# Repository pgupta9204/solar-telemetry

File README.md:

# Solar Telemetry: Sub-8g Avian Wildlife Telemetry Node

An ultra-lightweight ($<8.0\text{g}$), perpetually energy-autonomous telemetry beacon engineered for avian wildlife conservation and asset tracking. Colloquially conceived as a "Solar AirTag", the system is architected from the ground up to replace heavy, battery-limited commercial tags with a sub-GHz RF beacon powered by solar energy harvesting.

---

## 1. Architectural Motivation

### 1.1 Avian Wildlife Conservation & The 5% Mass Rule
In wildlife telemetry and ornithological research, animal welfare dictates strict physical constraints:
* **The 5% Body-Mass Rule:** International ethical guidelines require that any tracking apparatus must not exceed **3-5%** of the bird's total body mass. Exceeding this limit impairs flight biomechanics, elevates metabolic expenditure, disrupts hunting, and skews behavioral data.
* **The Target Demographic:** Small-to-medium raptors—such as the American Kestrel (*Falco sparverius*, adult mass 100-140g), small falcons, and migratory shorebirds—have historically been excluded from continuous tracking due to the sheer bulk of existing hardware.
* **Limitations of Existing Commercial Tags:** Commercial avian trackers typically weigh >15-30g, cost upwards of \$1,500, and rely on non-rechargeable primary lithium cells that die within months, requiring recapture or terminating studies prematurely.

This project addresses this conservation bottleneck by engineering a complete telemetry solution under **8.0g total mass** (with a bare-board electronic budget of <3.0g capable of indefinite operation via ambient solar energy.

### 1.2 Electrical Engineering Scope & Design Objectives
This repository encapsulates a complete hardware development lifecycle:
* **KiCad EDA Workflow:** Schematic capture, hierarchical netlist design, custom symbol/footprint creation with 3D STEP modeling, and 4-layer PCB layout.
* **Controlled-Impedance RF Routing:** $50\Omega$ coplanar waveguide design and $\Pi$-matching network synthesis for Sub-GHz ISM frequencies (915 MHz / 868 MHz).
* **Ultra-Low-Power (ULP) Power Architecture:** Integration of maximum power point tracking (MPPT) solar harvesting with sub-microamp quiescent sleep states.
* **Event-Driven Firmware Architecture:** Hardware-level asynchronous interrupt handling to decouple sensing from compute and transmission.

---

## 2. Engineering Criteria & Constraints

| Parameter | Target Constraint | Design Implementation |
| :--- | :--- | :--- |
| **Total System Mass** | $m \le 8.0\text{g}$ (Target: $6.4\text{g}$) | Lightweight 4-layer $0.8\text{mm}$ PCB, miniature passives, SLA resin enclosure. |
| **Power Autonomy** | Net-Positive Diurnal Balance ($\Delta E_{\text{day}} > 0$) | e-peas AEM10941 PMIC + flexible solar cell + 35 mAh LiPo buffer. |
| **Deep-Sleep Current** | $I_{\text{sleep}} \le 2.5\,\mu\text{A}$ at $3.3\text{V}$ | STM32WL55 in Stop2 mode ($1.2\,\mu\text{A}$) + LIS2DW12 low-power sensing ($0.38\,\mu\text{A}$). |
| **RF Carrier Frequency** | $915\,\text{MHz}$ (US) / $868\,\text{MHz}$ (EU) | Sub-GHz ISM band for extended line-of-sight propagation ($>5\text{-}15\\text{km}$). |
| **RF Trace Impedance** | $Z_0 = 50.0\,\Omega \pm 5\%$ | JLC7628 stackup microstrip trace geometry with continuous L2 ground plane. |
| **Board Footprint** | $20.0 \text{mm} \times 25.0 \text{mm}$ | High-density component placement (0402 passives, UFQFPN-48, QFN-28). |

### Strict Mass Budget Breakdown ($6.4\text{g}$ Target)

| Subsystem | Component Details | Allocated Mass |
| :--- | :--- | :--- |
| **Bare PCB** | 4-Layer FR4 ($0.8\text{mm}$ core, $20\text{mm} \times 25\text{mm}$) | $0.8\text{g}$ |
| **Core Electronics** | STM32WL55 SoC, LIS2DW12 IMU, 0402/0603 passives | $0.6\text{g}$ |
| **Energy Harvester** | e-peas AEM10941 PMIC + 3V flexible solar cell | $0.7\text{g}$ |
| **Energy Buffer** | $3.7\text{V}$ 35 mAh ultra-light LiPo pouch cell | $1.8\text{g}$ |
| **RF Antenna System** | $50\Omega$ $\Pi$-network + $8.2\text{cm}$ micro-wire monopole | $0.3\text{g}$ |
| **Protective Housing** | SLA 3D-printed light-cured resin ($0.8\text{mm}$ wall) | $2.2\text{g}$ |
| **TOTAL** | **Fully Assembled Telemetry Node** | **$6.4\text{g}$** |

---

## 3. Engineering Trade-offs & Architecture

```mermaid
flowchart TD
    SP["Flexible Solar Panel<br/>(3V Amorphous / GaAs)"] -->|Raw Harvest| PMIC["e-peas AEM10941 PMIC<br/>(Boost Converter + MPPT)"]
    BAT["35 mAh LiPo Battery<br/>(Energy Buffer)"] <-->|Charge / Discharge| PMIC
    
    PMIC -->|"HVOUT Regulated 3.3V Rail"| MCU["STM32WL55 SoC<br/>(Cortex-M4 + Sub-GHz Radio)"]
    PMIC -->|"HVOUT Regulated 3.3V Rail"| IMU["LIS2DW12 Accelerometer<br/>(Ultra-Low Power Sensing)"]
    
    IMU -->|"INT1 Hardware Interrupt<br/>(Motion Alarm)"| MCU
    IMU <-->|"SPI1 Bus (Telemetry Read)"| MCU
    
    MCU -->|"RFOUT (915 MHz, +14dBm)"| MATCH["50 Ohm Pi-Matching Network<br/>(Harmonic Suppression)"]
    MATCH -->|"Matched RF Feed"| ANT["8.2 cm Monopole Wire Antenna"]
```

### Trade-off 1: Ground-Based TDoA Triangulation vs. Onboard GNSS
* **The Problem:** Commercial GPS modules require 15-30 mA continuous current with cold-start Time-To-First-Fix (TTFF) durations between 15-45 seconds. Each location fix consumes 2.0-4.0 Joules, demanding a battery exceeding 10g and heavy ceramic patch antennas (>2g).
* **The Solution:** Offload localization to ground-based receiver arrays using **Time Difference of Arrival (TDoA)** multilateration. The tag acts purely as an RF beacon transmitting ultrashort 50ms sub-GHz bursts.
* **Energy Impact:** Reduces energy-per-transmission to $\approx 0.0033\\text{J}$ — a **>600x efficiency improvement** over GPS, eliminating onboard GPS hardware mass entirely.

### Trade-off 2: Integrated SoC (STM32WL55) vs. Discrete MCU + Transceiver
* **The Problem:** Separate MCU and RF transceiver chips require inter-chip SPI routing, redundant decoupling networks, duplicate crystals, and enlarged PCB real estate ($>300\\text{mm}^2$), increasing board mass and parasitic trace losses.
* **The Solution:** Selected the **STM32WL55JC**, integrating an ARM Cortex-M4/M0+ controller and a Semtech SX126x-derived Sub-GHz radio onto a single $5\text{mm} \times 5\text{mm}$ UFQFPN-48 die.
* **Benefit:** Shrinks RF front-end footprint by 40%, minimizes trace parasitic inductance, and eliminates MCU-to-radio bus latency.

### Trade-off 3: Solar MPPT PMIC (e-peas AEM10941) vs. Linear Charging
* **The Problem:** Lightweight flexible solar panels produce volatile open-circuit voltages (0.5-3.5V) and micro-currents under varied daylight and canopy shade, making standard linear battery chargers unusable.
* **The Solution:** The **e-peas AEM10941** features an ultra-low-power boost converter with an integrated Maximum Power Point Tracking (MPPT) state machine that operates down to 100mV input and cold-starts at 380mV. It provides dual regulated LDO outputs and overcharge/overdischarge protection for the 35 mAh buffer.

### Trade-off 4: Asynchronous Motion Wakeup (IMU EXTI) vs. Polling
* **The Problem:** Constantly waking the MCU to check sensors via timer polling would drain tens of microamps, depleting the miniature battery overnight.
* **The Solution:** The **ST LIS2DW12** 3-axis accelerometer runs independently in low-power mode (<0.4µA at 1.6 Hz ODR) monitoring acceleration thresholds. When movement occurs, its physical interrupt pin (`INT1`) asserts an asynchronous external interrupt (`PA0` / EXTI0) to pull the STM32WL55 out of deep sleep (Stop2 mode). The MCU transmits a telemetry burst, updates its counters, and immediately enters Stop2 sleep.

---

## 4. Technical Specifications & Governing Equations

### 4.1 RF Transmission Line & $50\Omega$ Microstrip Math
To ensure maximum power transfer and prevent reflective signal attenuation at $915\\text{MHz}$, the RF trace from `RFOUT_HP` through the $\Pi$-matching network to the antenna pad is calculated as a microstrip transmission line referencing an unbroken Layer 2 ground plane.

```
       Trace Width (W)
          |=======|      --- Copper Thickness (T = 0.035 mm)
=============================
  Dielectric Prepreg (H = 0.1064 mm, Er = 4.05)
-----------------------------
============================= Solid Ground Plane (L2)
```

Using the **IPC-2141 / Wheeler microstrip equations** with copper thickness correction:

$$W_{\text{eff}} = W + \frac{T}{\pi} \left( 1 + \ln\left( \frac{2H}{T} \right) \right)$$

$$u = \frac{W_{\text{eff}}}{H}$$

$$\epsilon_{\text{eff}} = \frac{\epsilon_r + 1}{2} + \frac{\epsilon_r - 1}{2} \cdot \frac{1}{\sqrt{1 + 12/u}}$$

For $u > 1$:
$$Z_0 = \frac{120\pi}{\sqrt{\epsilon_{\text{eff}}} \left[ u + 1.393 + 0.667 \ln(u + 1.444) \right]}$$

* **Stackup Parameters:** JLCPCB JLC7628 4-Layer ($0.8\\text{mm}$ thickness), $H = 0.1064\\text{mm}$, $T = 0.035\,\text{mm}$ ($1\\text{oz}$ copper), $\epsilon_r = 4.05$.
* **Synthesized Trace Width:** $W = 0.18\,\text{mm}$ ($7.1\,\text{mils}$) yields **$Z_0 = 50.0\\Omega$**.
* **Antenna Design:** Quarter-wavelength ($\lambda/4$) wire monopole:
  $$L_{\text{ant}} = \frac{c}{4f} = \frac{3 \times 10^8\\text{m/s}}{4 \times 915 \times 10^6\\text{Hz}} \approx 82.0\\text{mm} \; (8.2\\text{cm})$$

### 4.2 Diurnal Energy Balance & Power Autonomy
Perpetual operation requires that total harvested energy exceeds total system dissipation over 24 hours:

$$\Delta E_{\text{day}} = E_{\text{harvest}} - E_{\text{consumed}} > 0$$

#### Consumption Budget (24-Hour Cycle)
* **Sleep Mode ($23.999\\text{hours/day}$):**
  $$Q_{\text{sleep}} = I_{\text{sleep}} \cdot 24\\text{h} = 2.5\\mu\text{A} \times 24\\text{h} = 60.0\\mu\text{Ah}$$
* **Active RF Bursts ($50\text{ bursts/day}$ at $20\\text{mA}$, $50\\text{ms}$ duration):**
  $$Q_{\text{tx, burst}} = I_{\text{tx}} \cdot t_{\text{tx}} = 20\\text{mA} \times \left(\frac{0.05\\text{s}}{3600\\text{s/h}}\right) \approx 0.278\\mu\text{Ah}$$
  $$Q_{\text{tx, daily}} = 50 \times 0.278\\mu\text{Ah} \approx 13.9\\mu\text{Ah}$$
* **Total Daily Drain:**
  $$Q_{\text{total, consumed}} = 60.0\\mu\text{Ah} + 13.9\\mu\text{Ah} = \mathbf{73.9\\mu\text{Ah/day}} \; (0.074\\text{mAh/day})$$

#### Solar Harvesting Model
Using a miniature flexible solar panel producing peak current $I_{\text{sc}} = 350\\mu\text{A}$ across a 6-hour diurnal sunlight window with sinusoidal insolation:
$$t_{\text{effective}} = \frac{2}{\pi} \cdot t_{\text{sun}} = \frac{2}{\pi} \times 6.0\\text{h} \approx 3.82\\text{h}$$
$$Q_{\text{harvest, raw}} = 350\\mu\text{A} \times 3.82\\text{h} \approx 1337\\mu\text{Ah}$$
Accounting for PMIC boost conversion efficiency ($\eta_{\text{PMIC}} \approx 85\%$):
$$Q_{\text{harvest, stored}} = 1337\\mu\text{Ah} \times 0.85 = \mathbf{1136\\mu\text{Ah/day}} \; (1.14\\text{mAh/day})$$

#### Net Margin & Zero-Sun Endurance
$$\Delta Q_{\text{net}} = 1136\\mu\text{Ah} - 73.9\\mu\text{Ah} = \mathbf{+1062.1\\mu\text{Ah/day}} \; (\text{Net Positive})$$

With a 35 mAh LiPo buffer operating within an $80\%$ depth of discharge window ($28\\text{mAh}$ usable):
$$\text{Zero-Sunlight Autonomy} = \frac{28.0\\text{mAh}}{0.074\\text{mAh/day}} \approx \mathbf{378\\text{days of operation without sun}}$$

### 4.3 12-Byte Packed Telemetry Packet Architecture
To keep RF burst transmission duration strictly under $50\,\text{ms}$, telemetry data is structured as an aligned 12-byte binary payload:

```
 0        1        2        3        4        5        6        7        8        9       10       11
+--------+--------+--------+--------+--------+--------+--------+--------+--------+--------+--------+--------+
|   Device ID     |   Battery mV    |            Motion Count         |  Accel Z (mg)  | Reason | Status |
|    (uint16)     |    (uint16)     |              (uint32)           |    (int16)     | (uint8)| (uint8)|
+--------+--------+--------+--------+--------+--------+--------+--------+--------+--------+--------+--------+
```

---

## 5. Hardware Implementation & KiCad Project

All hardware files are developed in KiCad 8 and located in [`solar-airtag-kicad/`](./solar-airtag-kicad):

* **Schematic:** [`solar-airtag-kicad.kicad_sch`](./solar-airtag-kicad/solar-airtag-kicad.kicad_sch) — Full schematic with subcircuits for the AEM10941 PMIC, STM32WL55 SoC, LIS2DW12 IMU, 32MHz TCXO, and RF $\Pi$-matching filter.
* **PCB Layout:** [`solar-airtag-kicad.kicad_pcb`](./solar-airtag-kicad/solar-airtag-kicad.kicad_pcb) — 4-layer $20\text{mm} \times 25\text{mm}$ board layout with uninterrupted L2 GND reference plane.
* **Component Libraries:** [`libraries/`](./solar-airtag-kicad/libraries) — Custom verified schematic symbols, IPC-compliant footprints, and 3D STEP models for the AEM10941-QFN and LIS2DW12TR LGA-12.

---

## 6. Future Steps & Development Roadmap

1. **PCB Optimization & DRC Verification**
   - Refine RF coplanar waveguide routing and via fence ground stitching around the $915\,\text{MHz}$ trace.
   - Run complete Design Rule Checks (DRC) and Electrical Rule Checks (ERC) against JLCPCB 4-layer manufacturing constraints.
   - Panelize and export Gerber, drill, and centroid files for SMT assembly.

2. **Firmware & Software Development**
   - Initialize STM32WL55 bare-metal / RTOS project using STM32CubeIDE.
   - Implement low-power driver for LIS2DW12 (SPI communication, interrupt threshold configuration, and deep-sleep management).
   - Configure Sub-GHz radio HAL for FSK / LoRa packet transmission with configurable transmit power ($+10\text{dBm}\text{–}+14\text{dBm}$).
   - Program the power-management state machine around STM32 Stop2 mode with RTC backup timers.

3. **Bench Evaluation & Validation**
   - Validate power profiles using the **Nordic Power Profiler Kit II (PPK2)** to measure sub-2.5µA sleep currents and active burst profiles.
   - Verify solar harvesting and MPPT tracking using evaluation boards (**NUCLEO-WL55JC1** and **e-peas EVK10941**).
   - Characterize RF matching and return loss ($S_{11} < -15\\text{dB}$) on a Vector Network Analyzer (VNA).

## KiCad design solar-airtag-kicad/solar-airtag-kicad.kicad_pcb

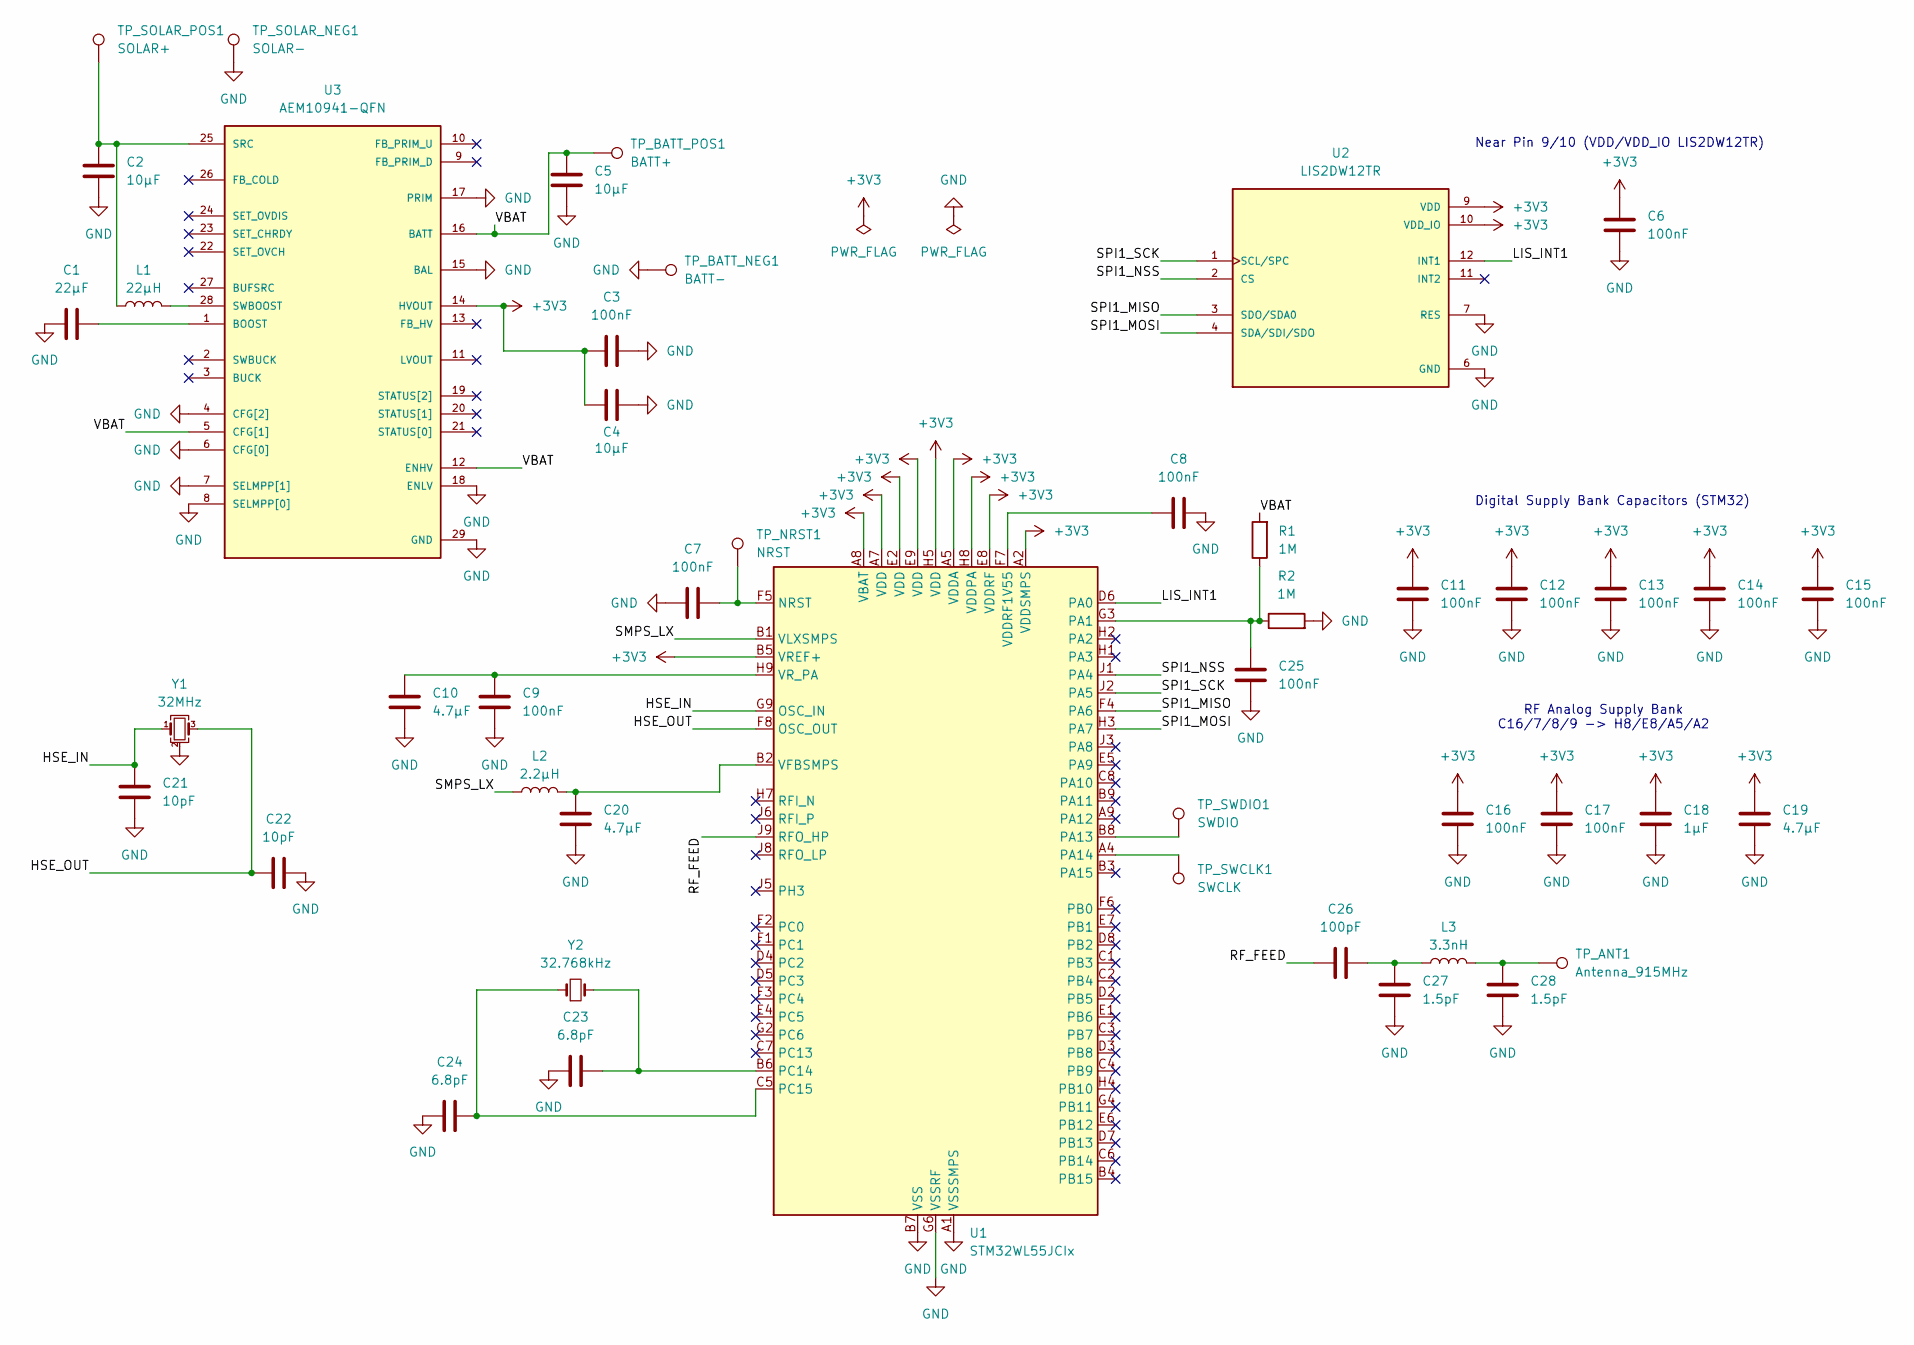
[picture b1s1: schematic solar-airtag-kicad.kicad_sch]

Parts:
C1: 22µF; C_0805_2012Metric
C2, C4, C5: 10µF; C_0603_1608Metric
C3, C6, C7, C8, C9, C11, C12, C13, C14, C15, C16, C17, C25: 100nF; C_0402_1005Metric
C10, C19, C20: 4.7µF; C_0603_1608Metric
C18: 1µF; C_0402_1005Metric
C21, C22: 10pF; C_0402_1005Metric
C23, C24: 6.8pF; C_0402_1005Metric
C26: 100pF; C_0402_1005Metric
C27, C28: 1.5pF; C_0402_1005Metric
L1: 22µH; L_0805_2012Metric
L2: 2.2µH; L_0805_2012Metric
L3: 3.3nH; L_0402_1005Metric
R1, R2: 1M; R_0402_1005Metric
TP_ANT1: Antenna_915MHz; TestPoint_Pad_D1.5mm
TP_BATT_NEG1: BATT-; TestPoint_Pad_D1.5mm
TP_BATT_POS1: BATT+; TestPoint_Pad_D1.5mm
TP_NRST1: NRST; TestPoint_Pad_D1.0mm
TP_SOLAR_NEG1: SOLAR-; TestPoint_Pad_D1.5mm
TP_SOLAR_POS1: SOLAR+; TestPoint_Pad_D1.5mm
TP_SWCLK1: SWCLK; TestPoint_Pad_D1.0mm
TP_SWDIO1: SWDIO; TestPoint_Pad_D1.0mm
U1: STM32WL55JCIx; ST_UFBGA-73_5x5mm_Layout9x9_P0.5mm
U2: LIS2DW12TR; LGA12R50P4X4_200X200X70; PARTREV 4
U3: AEM10941-QFN; QFN50P500X500X90-29N; PARTREV 1.4
Y1: 32MHz; Crystal_SMD_3225-4Pin_3.2x2.5mm
Y2: 32.768kHz; Crystal_SMD_3215-2Pin_3.2x1.5mm

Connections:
+3V3: C3.1, C4.1, C6.1, C11.1, C12.1, C13.1, C14.1, C15.1, C16.1, C17.1, C18.1, C19.1, U1.A2 (VDDSMPS), U1.A5 (VDDA), U1.A7 (VDD), U1.A8 (VBAT), U1.B5 (VREF+), U1.E2 (VDD), U1.E8 (VDDRF), U1.E9 (VDD), U1.H5 (VDD), U1.H8 (VDDPA), U2.9 (VDD), U2.10 (VDD_IO), U3.14 (HVOUT)
/HSE_IN: C21.1, U1.G9 (OSC_IN), Y1.1
/HSE_OUT: C22.1, U1.F8 (OSC_OUT), Y1.3
/LIS_INT1: U1.D6 (PA0), U2.12 (INT1)
/RF_FEED: C26.1, U1.J9 (RFO_HP)
/SMPS_LX: L2.1, U1.B1 (VLXSMPS)
/SPI1_MISO: U1.F4 (PA6), U2.3 (SDO/SDA0)
/SPI1_MOSI: U1.H3 (PA7), U2.4 (SDA/SDI/SDO)
/SPI1_NSS: U1.J1 (PA4), U2.2 (CS)
/SPI1_SCK: U1.J2 (PA5), U2.1 (SCL/SPC)
/VBAT: C5.1, R1.2, TP_BATT_POS1.1 (1_1), U3.5 (CFG[1]), U3.12 (ENHV), U3.16 (BATT)
GND: C1.1, C2.2, C3.2, C4.2, C5.2, C6.2, C7.1, C8.1, C9.2, C10.1, C11.2, C12.2, C13.2, C14.2, C15.2, C16.2, C17.2, C18.2, C19.2, C20.2, C21.2, C22.2, C23.1, C24.1, C25.2, C27.2, C28.2, R2.2, TP_BATT_NEG1.1 (1_1), TP_SOLAR_NEG1.1 (1_1), U1.A1 (VSSSMPS), U1.B7 (VSS), U1.D9 (VSS), U1.E3 (VSS), U1.G5 (VSS), U1.G6 (VSSRF), U1.G7 (VSSRF), U1.G8 (VSSRF), U1.H6 (VSSRF), U2.6 (GND), U2.7 (RES), U2.8 (GND), U3.4 (CFG[2]), U3.6 (CFG[0]), U3.7 (SELMPP[1]), U3.8 (SELMPP[0]), U3.15 (BAL), U3.17 (PRIM), U3.18 (ENLV), U3.29 (GND), Y1.2 (G), Y1.4 (G)
unnamed: C26.2, C27.1, L3.1
unnamed: C28.1, L3.2, TP_ANT1.1 (1_1)
unnamed: C7.2, TP_NRST1.1 (1_1), U1.F5 (NRST)
unnamed: C25.1, R1.1, R2.1, U1.G3 (PA1)
unnamed: TP_SWDIO1.1 (1_1), U1.B8 (PA13)
unnamed: TP_SWCLK1.1 (1_1), U1.A4 (PA14)
unnamed: C23.2, U1.B6 (PC14), Y2.2
unnamed: C24.2, U1.C5 (PC15), Y2.1
unnamed: C8.2, U1.F7 (VDDRF1V55)
unnamed: C20.1, L2.2, U1.B2 (VFBSMPS)
unnamed: C9.1, C10.2, U1.H9 (VR_PA)
unnamed: C1.2, U3.1 (BOOST)
unnamed: C2.1, L1.1, TP_SOLAR_POS1.1 (1_1), U3.25 (SRC)
unnamed: L1.2, U3.28 (SWBOOST)

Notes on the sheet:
RF Analog Supply Bank C16/7/8/9 -> H8/E8/A5/A2
Digital Supply Bank Capacitors (STM32)
Near Pin 9/10 (VDD/VDD_IO LIS2DW12TR)

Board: 4 copper layers, 46 parts (0 on the bottom side), 26 nets, no tracks yet.
